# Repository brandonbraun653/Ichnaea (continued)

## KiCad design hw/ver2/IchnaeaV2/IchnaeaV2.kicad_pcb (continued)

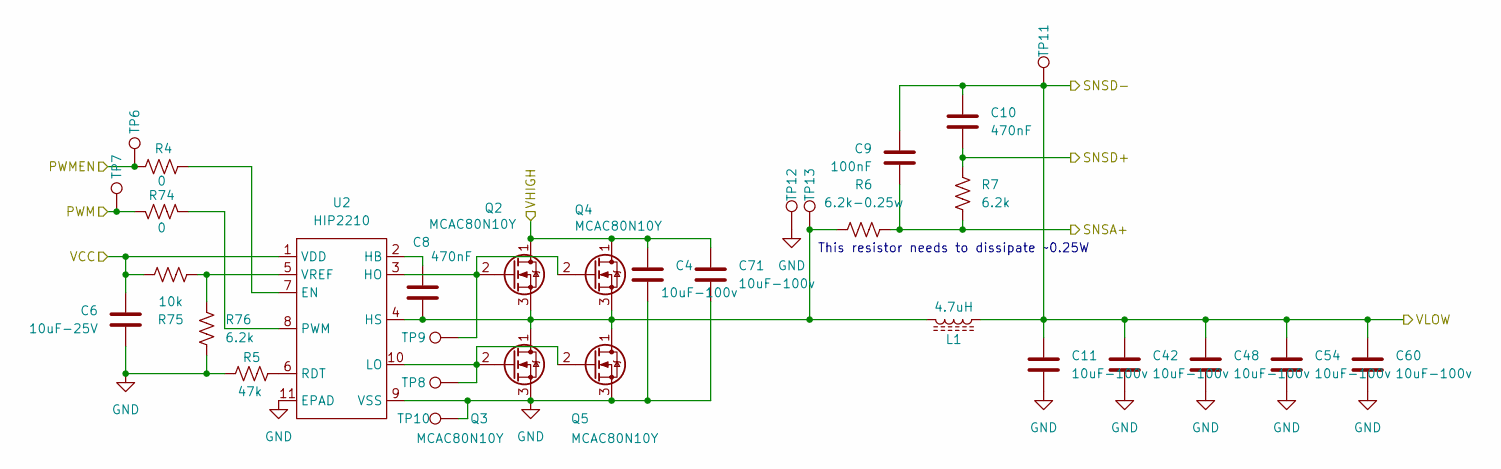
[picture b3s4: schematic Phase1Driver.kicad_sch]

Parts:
C4, C11, C42, C48, C54, C60, C71: 10uF-100v; C_1210_3225Metric_Pad1.33x2.70mm_HandSolder; Digikey 445-CGA6P1X7R1N106M250ACCT-ND
C6: 10uF-25V; C_0603_1608Metric; Digikey N/A
C8, C10: 470nF; C_0603_1608Metric; Digikey N/A
C9: 100nF; C_0603_1608Metric; LCSC C14663
L1: 4.7uH; Bournes_L_PQ2614BLA; Digikey PQ2614BLA-3R3K-ND
Q2, Q3, Q4, Q5: MCAC80N10Y; TRANS_BSC076N06NS3-G; Digikey 353-MCAC80N10Y-TPCT-ND
R4, R74: 0; R_0603_1608Metric; Digikey N/A
R5: 47k; R_0603_1608Metric; Digikey N/A
R6: 6.2k-0.25w; R_1206_3216Metric_Pad1.30x1.75mm_HandSolder; Digikey 311-6.20KFRCT-ND
R7, R76: 6.2k; R_0603_1608Metric; Digikey N/A
R75: 10k; R_0603_1608Metric; LCSC C25804
TP6, TP7, TP8, TP9, TP10, TP11, TP12, TP13: TestPoint; TestPoint_Pad_D1.0mm
U2: HIP2210; TDFN-10-1EP_4x4mm_P0.8mm_EP2.6x3mm; Digikey 20-HIP2210FRTZ-TCT-ND

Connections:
+12V: C6.1, R75.1, U2.1 (VDD); also elsewhere on the board
/PowerStage/Phase1/PWM: R74.2, TP7.1; also elsewhere on the board
/PowerStage/Phase1/PWMEN: R4.2, TP6.1; also elsewhere on the board
/PowerStage/Phase1/SNSA+: C9.2, R6.2, R7.2; also elsewhere on the board
/PowerStage/Phase1/SNSD+: C10.2, R7.1; also elsewhere on the board
GND: C4.2, C6.2, C11.2, C42.2, C48.2, C54.2, C60.2, C71.2, Q3.3 (S), Q5.3 (S), R5.1, R76.2, TP10.1, TP12.1, U2.9 (VSS), U2.11 (EPAD); also elsewhere on the board
unnamed: Q2.2 (G), Q4.2 (G), TP9.1, U2.3 (HO)
unnamed: C8.2, L1.2, Q2.3 (S), Q3.1 (D), Q4.3 (S), Q5.1 (D), R6.1, TP13.1, U2.4 (HS)
unnamed: Q3.2 (G), Q5.2 (G), TP8.1, U2.10 (LO)
unnamed: R4.1, U2.7 (EN)
unnamed: C8.1, U2.2 (HB)
unnamed: R74.1, U2.8 (PWM)
unnamed: R5.2, U2.6 (RDT)
unnamed: R75.2, R76.1, U2.5 (VREF)
VHIGH: C4.1, C71.1, Q2.1 (D), Q4.1 (D); also elsewhere on the board
VLOW: C9.1, C10.1, C11.1, C42.1, C48.1, C54.1, C60.1, L1.1, TP11.1; also elsewhere on the board

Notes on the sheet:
This resistor needs to dissipate ~0.25W

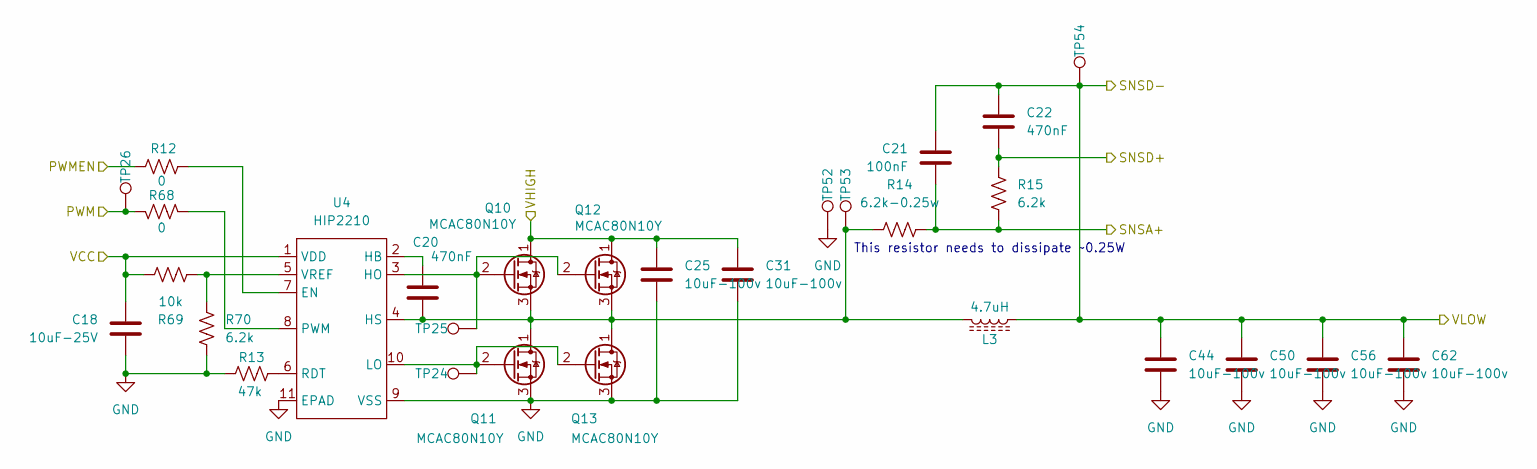
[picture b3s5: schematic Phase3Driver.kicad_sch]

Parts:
C18: 10uF-25V; C_0603_1608Metric; Digikey N/A
C20, C22: 470nF; C_0603_1608Metric; Digikey N/A
C21: 100nF; C_0603_1608Metric; LCSC C14663
C25, C31, C44, C50, C56, C62: 10uF-100v; C_1210_3225Metric_Pad1.33x2.70mm_HandSolder; Digikey 445-CGA6P1X7R1N106M250ACCT-ND
L3: 4.7uH; Bournes_L_PQ2614BLA; Digikey PQ2614BLA-3R3K-ND
Q10, Q11, Q12, Q13: MCAC80N10Y; TRANS_BSC076N06NS3-G; Digikey 353-MCAC80N10Y-TPCT-ND
R12, R68: 0; R_0603_1608Metric; Digikey N/A
R13: 47k; R_0603_1608Metric; Digikey N/A
R14: 6.2k-0.25w; R_1206_3216Metric_Pad1.30x1.75mm_HandSolder; Digikey 311-6.20KFRCT-ND
R15, R70: 6.2k; R_0603_1608Metric; Digikey N/A
R69: 10k; R_0603_1608Metric; LCSC C25804
TP24, TP25, TP26, TP52, TP53, TP54: TestPoint; TestPoint_Pad_D1.0mm
U4: HIP2210; TDFN-10-1EP_4x4mm_P0.8mm_EP2.6x3mm; Digikey 20-HIP2210FRTZ-TCT-ND

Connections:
+12V: C18.1, R69.1, U4.1 (VDD); also elsewhere on the board
/PowerStage/Phase1/PWMEN: R12.2; also elsewhere on the board
/PowerStage/Phase3/PWM: R68.2, TP26.1; also elsewhere on the board
/PowerStage/Phase3/SNSA+: C21.2, R14.2, R15.2; also elsewhere on the board
/PowerStage/Phase3/SNSD+: C22.2, R15.1; also elsewhere on the board
GND: C18.2, C25.2, C31.2, C44.2, C50.2, C56.2, C62.2, Q11.3 (S), Q13.3 (S), R13.1, R70.2, TP52.1, U4.9 (VSS), U4.11 (EPAD); also elsewhere on the board
unnamed: Q10.2 (G), Q12.2 (G), TP25.1, U4.3 (HO)
unnamed: C20.2, L3.2, Q10.3 (S), Q11.1 (D), Q12.3 (S), Q13.1 (D), R14.1, TP53.1, U4.4 (HS)
unnamed: Q11.2 (G), Q13.2 (G), TP24.1, U4.10 (LO)
unnamed: R12.1, U4.7 (EN)
unnamed: C20.1, U4.2 (HB)
unnamed: R68.1, U4.8 (PWM)
unnamed: R13.2, U4.6 (RDT)
unnamed: R69.2, R70.1, U4.5 (VREF)
VHIGH: C25.1, C31.1, Q10.1 (D), Q12.1 (D); also elsewhere on the board
VLOW: C21.1, C22.1, C44.1, C50.1, C56.1, C62.1, L3.1, TP54.1; also elsewhere on the board

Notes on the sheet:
This resistor needs to dissipate ~0.25W

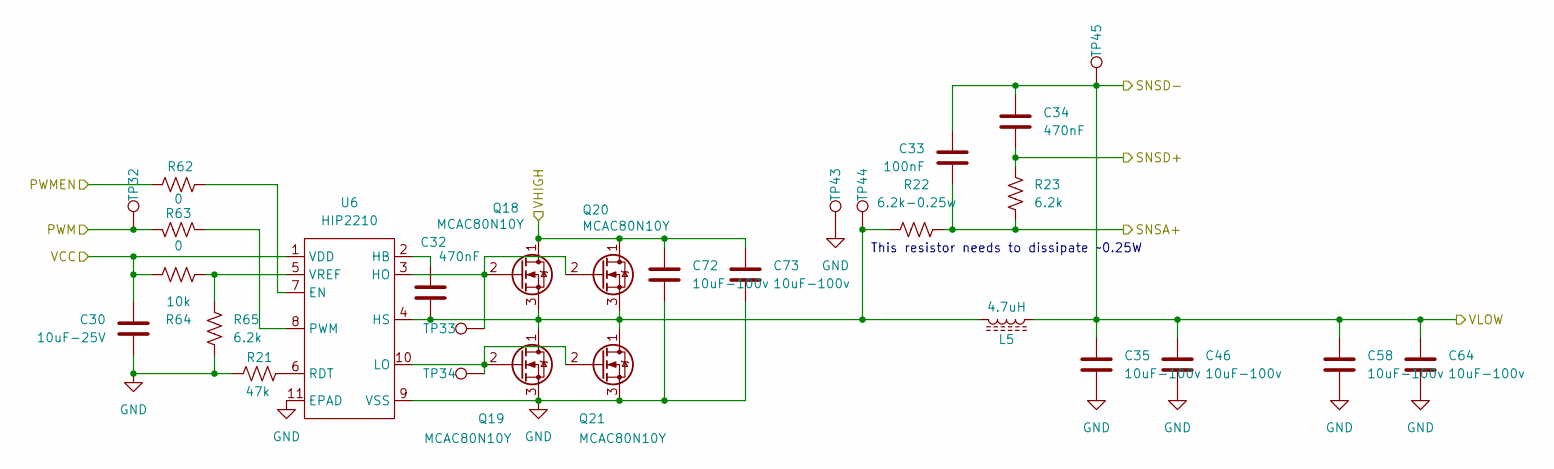
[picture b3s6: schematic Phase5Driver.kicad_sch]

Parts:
C30: 10uF-25V; C_0603_1608Metric; Digikey N/A
C32, C34: 470nF; C_0603_1608Metric; Digikey N/A
C33: 100nF; C_0603_1608Metric; LCSC C14663
C35, C46, C58, C64, C72, C73: 10uF-100v; C_1210_3225Metric_Pad1.33x2.70mm_HandSolder; Digikey 445-CGA6P1X7R1N106M250ACCT-ND
L5: 4.7uH; Bournes_L_PQ2614BLA; Digikey PQ2614BLA-3R3K-ND
Q18, Q19, Q20, Q21: MCAC80N10Y; TRANS_BSC076N06NS3-G; Digikey 353-MCAC80N10Y-TPCT-ND
R21: 47k; R_0603_1608Metric; Digikey N/A
R22: 6.2k-0.25w; R_1206_3216Metric_Pad1.30x1.75mm_HandSolder; Digikey 311-6.20KFRCT-ND
R23, R65: 6.2k; R_0603_1608Metric; Digikey N/A
R62, R63: 0; R_0603_1608Metric; Digikey N/A
R64: 10k; R_0603_1608Metric; LCSC C25804
TP32, TP33, TP34, TP43, TP44, TP45: TestPoint; TestPoint_Pad_D1.0mm
U6: HIP2210; TDFN-10-1EP_4x4mm_P0.8mm_EP2.6x3mm; Digikey 20-HIP2210FRTZ-TCT-ND

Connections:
+12V: C30.1, R64.1, U6.1 (VDD); also elsewhere on the board
/PowerStage/Phase1/PWMEN: R62.2; also elsewhere on the board
/PowerStage/Phase5/PWM: R63.2, TP32.1; also elsewhere on the board
/PowerStage/Phase5/SNSA+: C33.2, R22.2, R23.2; also elsewhere on the board
/PowerStage/Phase5/SNSD+: C34.2, R23.1; also elsewhere on the board
GND: C30.2, C35.2, C46.2, C58.2, C64.2, C72.2, C73.2, Q19.3 (S), Q21.3 (S), R21.1, R65.2, TP43.1, U6.9 (VSS), U6.11 (EPAD); also elsewhere on the board
unnamed: Q18.2 (G), Q20.2 (G), TP33.1, U6.3 (HO)
unnamed: C32.2, L5.2, Q18.3 (S), Q19.1 (D), Q20.3 (S), Q21.1 (D), R22.1, TP44.1, U6.4 (HS)
unnamed: Q19.2 (G), Q21.2 (G), TP34.1, U6.10 (LO)
unnamed: R62.1, U6.7 (EN)
unnamed: C32.1, U6.2 (HB)
unnamed: R63.1, U6.8 (PWM)
unnamed: R21.2, U6.6 (RDT)
unnamed: R64.2, R65.1, U6.5 (VREF)
VHIGH: C72.1, C73.1, Q18.1 (D), Q20.1 (D); also elsewhere on the board
VLOW: C33.1, C34.1, C35.1, C46.1, C58.1, C64.1, L5.1, TP45.1; also elsewhere on the board

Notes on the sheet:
This resistor needs to dissipate ~0.25W

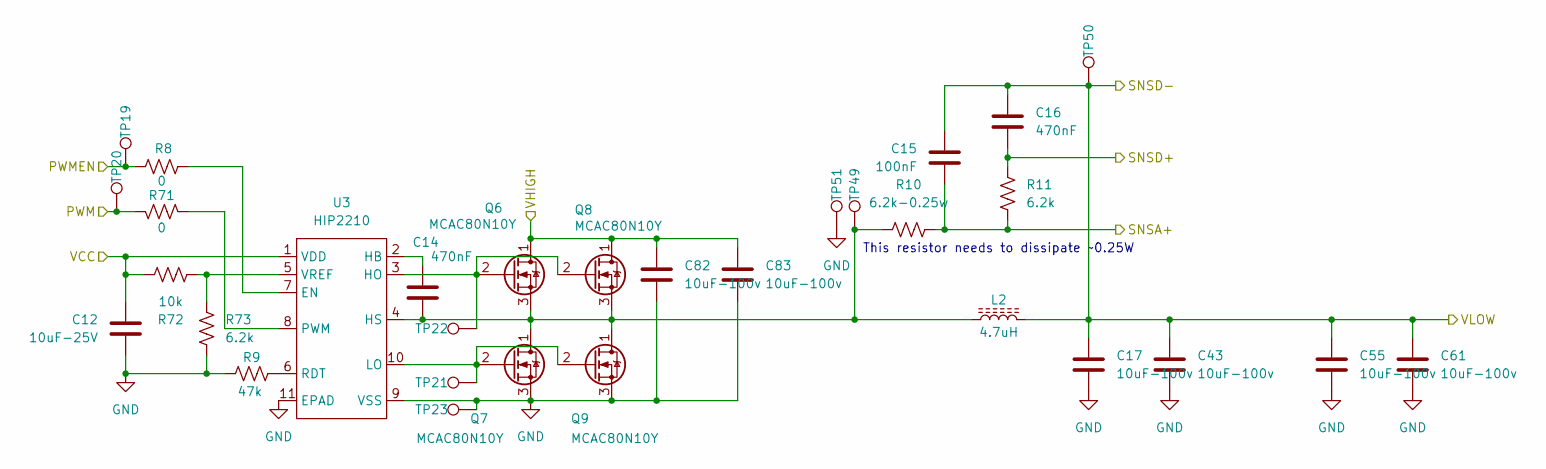
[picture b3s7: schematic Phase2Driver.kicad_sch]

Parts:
C12: 10uF-25V; C_0603_1608Metric; Digikey N/A
C14, C16: 470nF; C_0603_1608Metric; Digikey N/A
C15: 100nF; C_0603_1608Metric; LCSC C14663
C17, C43, C55, C61, C82, C83: 10uF-100v; C_1210_3225Metric_Pad1.33x2.70mm_HandSolder; Digikey 445-CGA6P1X7R1N106M250ACCT-ND
L2: 4.7uH; Bournes_L_PQ2614BLA; Digikey PQ2614BLA-3R3K-ND
Q6, Q7, Q8, Q9: MCAC80N10Y; TRANS_BSC076N06NS3-G; Digikey 353-MCAC80N10Y-TPCT-ND
R8, R71: 0; R_0603_1608Metric; Digikey N/A
R9: 47k; R_0603_1608Metric; Digikey N/A
R10: 6.2k-0.25w; R_1206_3216Metric_Pad1.30x1.75mm_HandSolder; Digikey 311-6.20KFRCT-ND
R11, R73: 6.2k; R_0603_1608Metric; Digikey N/A
R72: 10k; R_0603_1608Metric; LCSC C25804
TP19, TP20, TP21, TP22, TP23, TP49, TP50, TP51: TestPoint; TestPoint_Pad_D1.0mm
U3: HIP2210; TDFN-10-1EP_4x4mm_P0.8mm_EP2.6x3mm; Digikey 20-HIP2210FRTZ-TCT-ND

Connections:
+12V: C12.1, R72.1, U3.1 (VDD); also elsewhere on the board
/PowerStage/Phase1/PWMEN: R8.2, TP19.1; also elsewhere on the board
/PowerStage/Phase2/PWM: R71.2, TP20.1; also elsewhere on the board
/PowerStage/Phase2/SNSA+: C15.2, R10.2, R11.2; also elsewhere on the board
/PowerStage/Phase2/SNSD+: C16.2, R11.1; also elsewhere on the board
GND: C12.2, C17.2, C43.2, C55.2, C61.2, C82.2, C83.2, Q7.3 (S), Q9.3 (S), R9.1, R73.2, TP23.1, TP51.1, U3.9 (VSS), U3.11 (EPAD); also elsewhere on the board
unnamed: Q6.2 (G), Q8.2 (G), TP22.1, U3.3 (HO)
unnamed: C14.2, L2.1, Q6.3 (S), Q7.1 (D), Q8.3 (S), Q9.1 (D), R10.1, TP49.1, U3.4 (HS)
unnamed: Q7.2 (G), Q9.2 (G), TP21.1, U3.10 (LO)
unnamed: R8.1, U3.7 (EN)
unnamed: C14.1, U3.2 (HB)
unnamed: R71.1, U3.8 (PWM)
unnamed: R9.2, U3.6 (RDT)
unnamed: R72.2, R73.1, U3.5 (VREF)
VHIGH: C82.1, C83.1, Q6.1 (D), Q8.1 (D); also elsewhere on the board
VLOW: C15.1, C16.1, C17.1, C43.1, C55.1, C61.1, L2.2, TP50.1; also elsewhere on the board

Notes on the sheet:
This resistor needs to dissipate ~0.25W

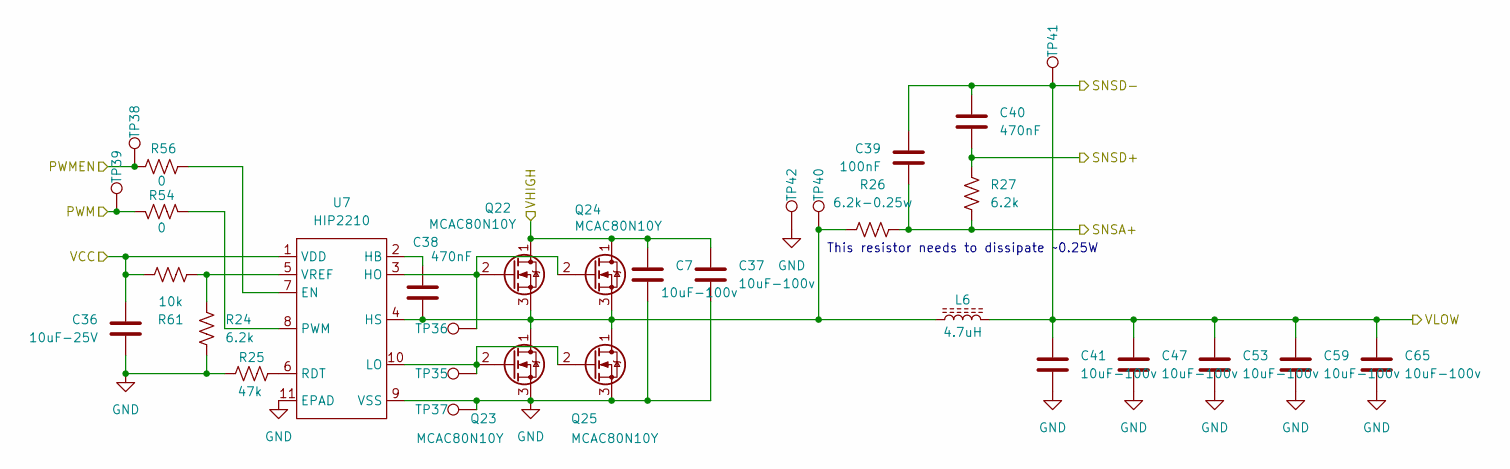
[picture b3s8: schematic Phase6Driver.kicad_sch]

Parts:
C7, C37, C41, C47, C53, C59, C65: 10uF-100v; C_1210_3225Metric_Pad1.33x2.70mm_HandSolder; Digikey 445-CGA6P1X7R1N106M250ACCT-ND
C36: 10uF-25V; C_0603_1608Metric; Digikey N/A
C38, C40: 470nF; C_0603_1608Metric; Digikey N/A
C39: 100nF; C_0603_1608Metric; LCSC C14663
L6: 4.7uH; Bournes_L_PQ2614BLA; Digikey PQ2614BLA-3R3K-ND
Q22, Q23, Q24, Q25: MCAC80N10Y; TRANS_BSC076N06NS3-G; Digikey 353-MCAC80N10Y-TPCT-ND
R24, R27: 6.2k; R_0603_1608Metric; Digikey N/A
R25: 47k; R_0603_1608Metric; Digikey N/A
R26: 6.2k-0.25w; R_1206_3216Metric_Pad1.30x1.75mm_HandSolder; Digikey 311-6.20KFRCT-ND
R54, R56: 0; R_0603_1608Metric; Digikey N/A
R61: 10k; R_0603_1608Metric; LCSC C25804
TP35, TP36, TP37, TP38, TP39, TP40, TP41, TP42: TestPoint; TestPoint_Pad_D1.0mm
U7: HIP2210; TDFN-10-1EP_4x4mm_P0.8mm_EP2.6x3mm; Digikey 20-HIP2210FRTZ-TCT-ND

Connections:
+12V: C36.1, R61.1, U7.1 (VDD); also elsewhere on the board
/PowerStage/Phase1/PWMEN: R56.2, TP38.1; also elsewhere on the board
/PowerStage/Phase6/PWM: R54.2, TP39.1; also elsewhere on the board
/PowerStage/Phase6/SNSA+: C39.2, R26.2, R27.2; also elsewhere on the board
/PowerStage/Phase6/SNSD+: C40.2, R27.1; also elsewhere on the board
GND: C7.2, C36.2, C37.2, C41.2, C47.2, C53.2, C59.2, C65.2, Q23.3 (S), Q25.3 (S), R24.2, R25.1, TP37.1, TP42.1, U7.9 (VSS), U7.11 (EPAD); also elsewhere on the board
unnamed: Q22.2 (G), Q24.2 (G), TP36.1, U7.3 (HO)
unnamed: C38.2, L6.1, Q22.3 (S), Q23.1 (D), Q24.3 (S), Q25.1 (D), R26.1, TP40.1, U7.4 (HS)
unnamed: Q23.2 (G), Q25.2 (G), TP35.1, U7.10 (LO)
unnamed: R56.1, U7.7 (EN)
unnamed: C38.1, U7.2 (HB)
unnamed: R54.1, U7.8 (PWM)
unnamed: R25.2, U7.6 (RDT)
unnamed: R24.1, R61.2, U7.5 (VREF)
VHIGH: C7.1, C37.1, Q22.1 (D), Q24.1 (D); also elsewhere on the board
VLOW: C39.1, C40.1, C41.1, C47.1, C53.1, C59.1, C65.1, L6.2, TP41.1; also elsewhere on the board

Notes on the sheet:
This resistor needs to dissipate ~0.25W

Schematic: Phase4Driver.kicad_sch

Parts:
C13, C19, C45, C51, C57, C63: 10uF-100v; C_1210_3225Metric_Pad1.33x2.70mm_HandSolder; Digikey 445-CGA6P1X7R1N106M250ACCT-ND
C24: 10uF-25V; C_0603_1608Metric; Digikey N/A
C26, C28: 470nF; C_0603_1608Metric; Digikey N/A
C27: 100nF; C_0603_1608Metric; LCSC C14663
L4: 4.7uH; Bournes_L_PQ2614BLA; Digikey PQ2614BLA-3R3K-ND
Q14, Q15, Q16, Q17: MCAC80N10Y; TRANS_BSC076N06NS3-G; Digikey 353-MCAC80N10Y-TPCT-ND
R16, R20: 0; R_0603_1608Metric; Digikey N/A
R17: 47k; R_0603_1608Metric; Digikey N/A
R18: 6.2k-0.25w; R_1206_3216Metric_Pad1.30x1.75mm_HandSolder; Digikey 311-6.20KFRCT-ND
R19, R67: 6.2k; R_0603_1608Metric; Digikey N/A
R66: 10k; R_0603_1608Metric; LCSC C25804
TP27, TP28, TP29, TP30, TP31, TP46, TP47, TP48: TestPoint; TestPoint_Pad_D1.0mm
U5: HIP2210; TDFN-10-1EP_4x4mm_P0.8mm_EP2.6x3mm; Digikey 20-HIP2210FRTZ-TCT-ND

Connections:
+12V: C24.1, R66.1, U5.1 (VDD); also elsewhere on the board
/PowerStage/Phase1/PWMEN: R16.2, TP30.1; also elsewhere on the board
/PowerStage/Phase4/PWM: R20.2, TP31.1; also elsewhere on the board
/PowerStage/Phase4/SNSA+: C27.2, R18.2, R19.2; also elsewhere on the board
/PowerStage/Phase4/SNSD+: C28.2, R19.1; also elsewhere on the board
GND: C13.2, C19.2, C24.2, C45.2, C51.2, C57.2, C63.2, Q15.3 (S), Q17.3 (S), R17.1, R67.2, TP29.1, TP46.1, U5.9 (VSS), U5.11 (EPAD); also elsewhere on the board
unnamed: Q14.2 (G), Q16.2 (G), TP27.1, U5.3 (HO)
unnamed: C26.2, L4.1, Q14.3 (S), Q15.1 (D), Q16.3 (S), Q17.1 (D), R18.1, TP47.1, U5.4 (HS)
unnamed: Q15.2 (G), Q17.2 (G), TP28.1, U5.10 (LO)
unnamed: R16.1, U5.7 (EN)
unnamed: C26.1, U5.2 (HB)
unnamed: R20.1, U5.8 (PWM)
unnamed: R17.2, U5.6 (RDT)
unnamed: R66.2, R67.1, U5.5 (VREF)
VHIGH: C13.1, C19.1, Q14.1 (D), Q16.1 (D); also elsewhere on the board
VLOW: C27.1, C28.1, C45.1, C51.1, C57.1, C63.1, L4.2, TP48.1; also elsewhere on the board

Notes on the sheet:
This resistor needs to dissipate ~0.25W

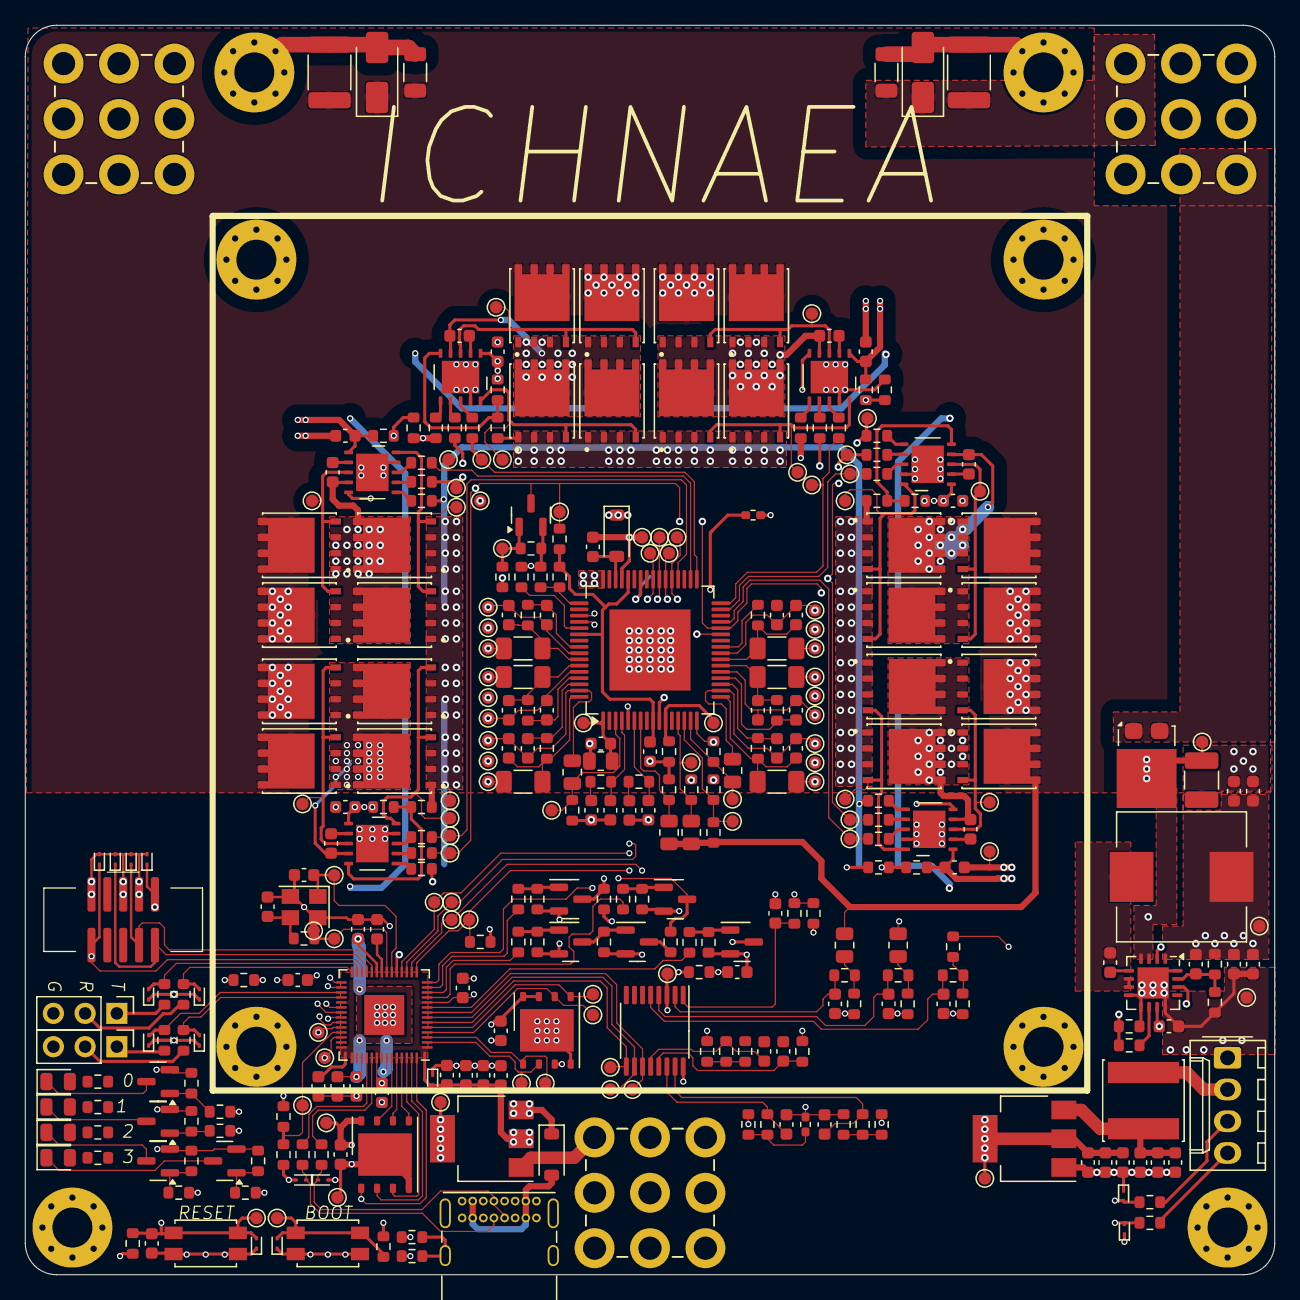
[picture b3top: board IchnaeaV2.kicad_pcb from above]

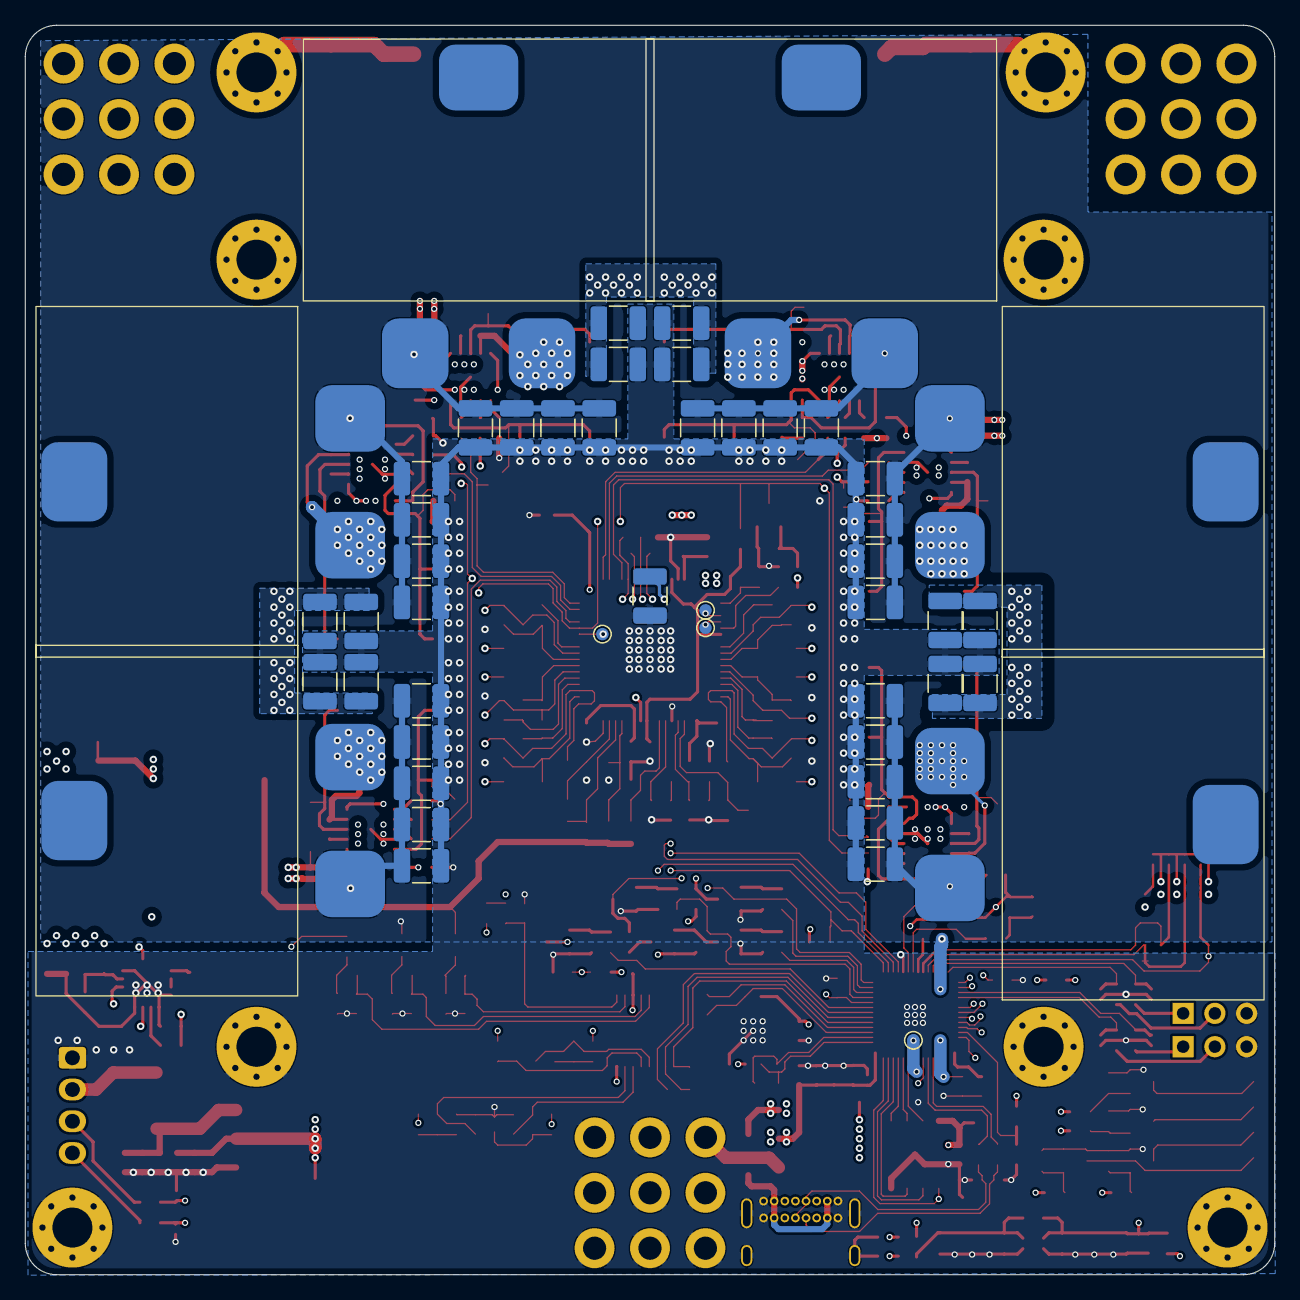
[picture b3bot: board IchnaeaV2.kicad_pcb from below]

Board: 4 copper layers, 100.0 x 100.0 mm, 430 parts (49 on the bottom side), 189 nets.

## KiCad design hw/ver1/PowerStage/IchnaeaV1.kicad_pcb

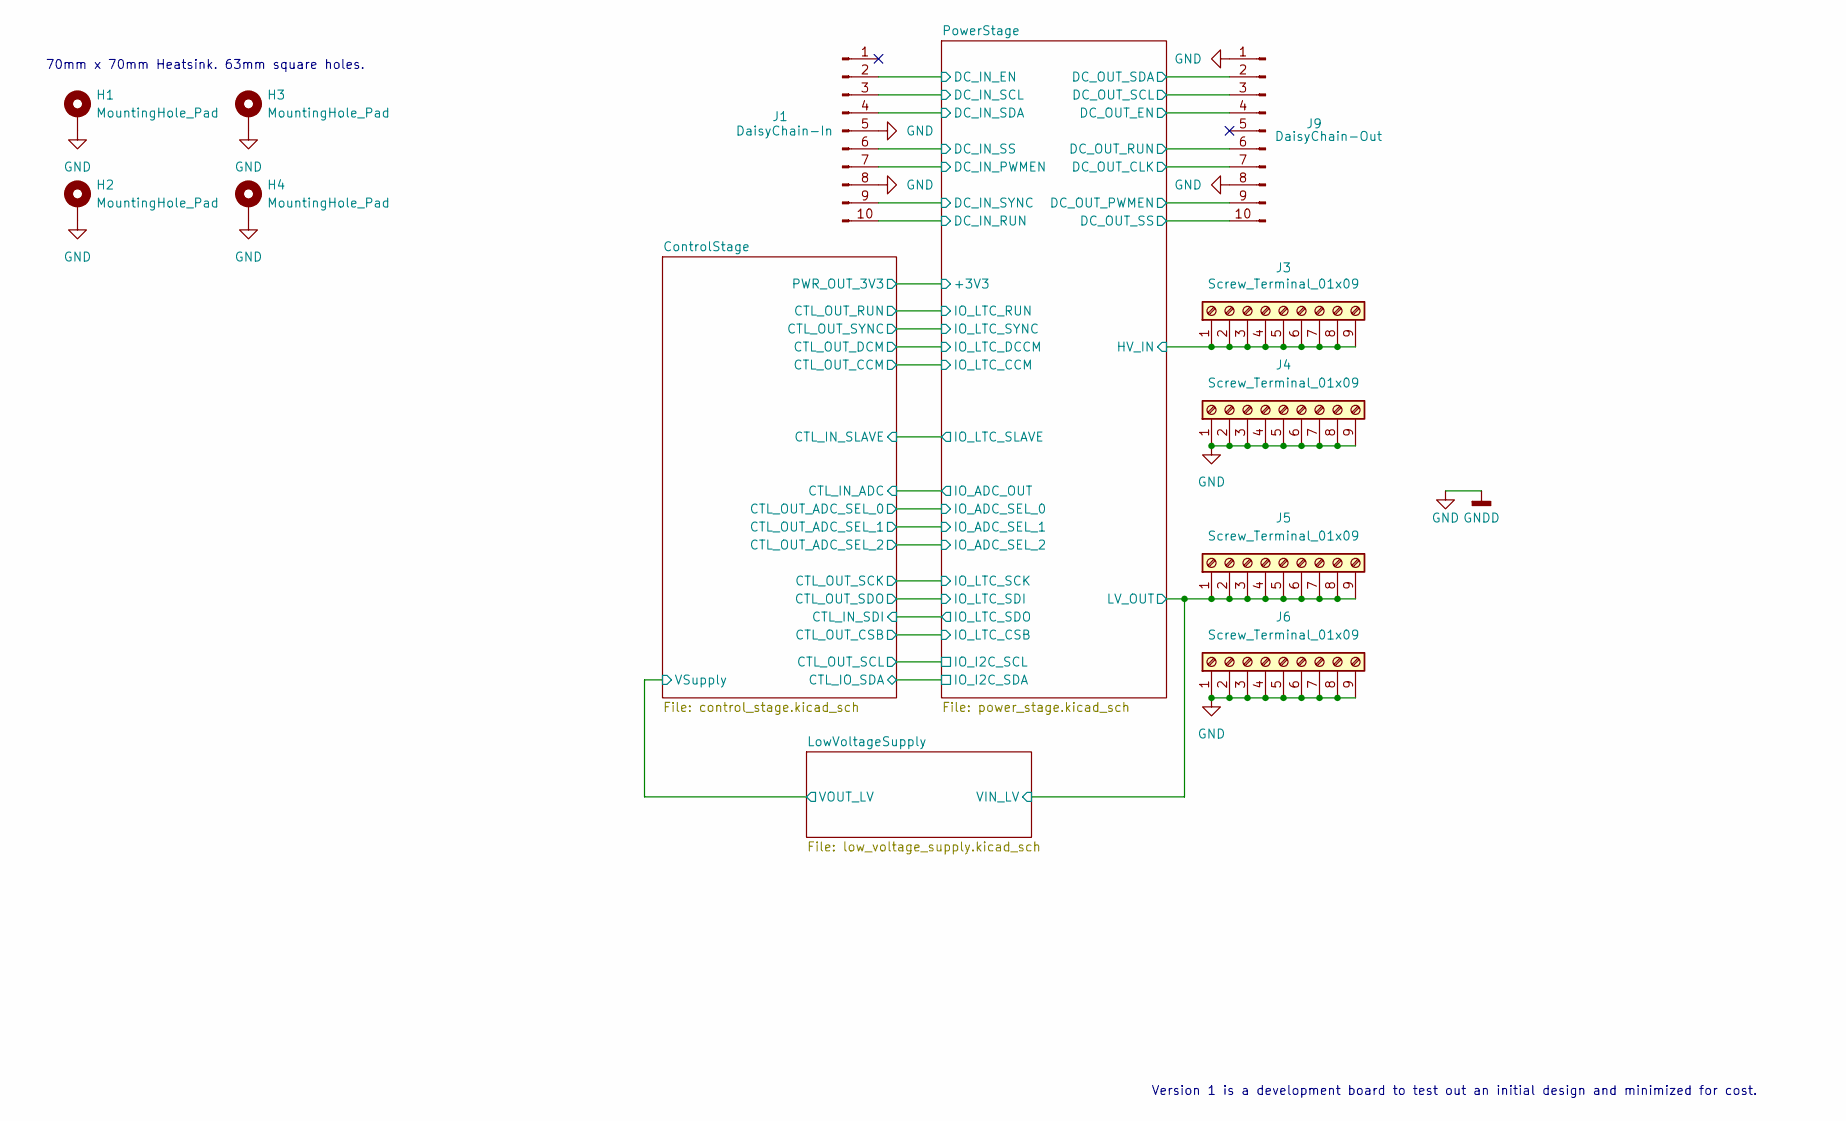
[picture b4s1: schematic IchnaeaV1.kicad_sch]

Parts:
H1, H2, H3, H4: MountingHole_Pad; MountingHole_3.2mm_M3_Pad_Via; Digikey N/A
J1: DaisyChain-In; JTAG_2x05_P1_27mm_Shrouded_SMD; Digikey 1175-1629-ND
J3, J4, J5, J6: Screw_Terminal_01x09; CONN_74651195R_WRE; Digikey 732-74651195RCT-ND
J9: DaisyChain-Out; JTAG_2x05_P1_27mm_Shrouded_SMD; Digikey 1175-1629-ND

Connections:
/ControlStage/CTL_IO_SDA: J1.4, J9.2; also elsewhere on the board
/ControlStage/CTL_OUT_SCL: J1.3, J9.3; also elsewhere on the board
/PowerStage/DC_IN_EN: J1.2; also elsewhere on the board
/PowerStage/DC_IN_PWMEN: J1.7; also elsewhere on the board
/PowerStage/DC_IN_RUN: J1.10; also elsewhere on the board
/PowerStage/DC_IN_SYNC: J1.9; also elsewhere on the board
/PowerStage/DC_OUT_CLK: J9.7; also elsewhere on the board
/PowerStage/DC_OUT_EN: J9.4; also elsewhere on the board
/PowerStage/DC_OUT_PWMEN: J9.9; also elsewhere on the board
/PowerStage/DC_OUT_RUN: J9.6; also elsewhere on the board
GND: H1.1, H2.1, H3.1, H4.1, J1.5, J1.8, J4.1, J4.2, J4.3, J4.4, J4.5, J4.6, J4.7, J4.8, J4.9, J6.1, J6.2, J6.3, J6.4, J6.5, J6.6, J6.7, J6.8, J6.9, J9.1, J9.8; also elsewhere on the board
HT: J3.1, J3.2, J3.3, J3.4, J3.5, J3.6, J3.7, J3.8, J3.9; also elsewhere on the board
LTC_SS: J1.6, J9.10; also elsewhere on the board
VLOW: J5.1, J5.2, J5.3, J5.4, J5.5, J5.6, J5.7, J5.8, J5.9; also elsewhere on the board

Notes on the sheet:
70mm x 70mm Heatsink. 63mm square holes.
Version 1 is a development board to test out an initial design and minimized for cost.
